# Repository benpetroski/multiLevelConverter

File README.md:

# multiLevelConverter
A Multi-Level Converter Topology

Email benjaminpetroski@gmail.com with questions.

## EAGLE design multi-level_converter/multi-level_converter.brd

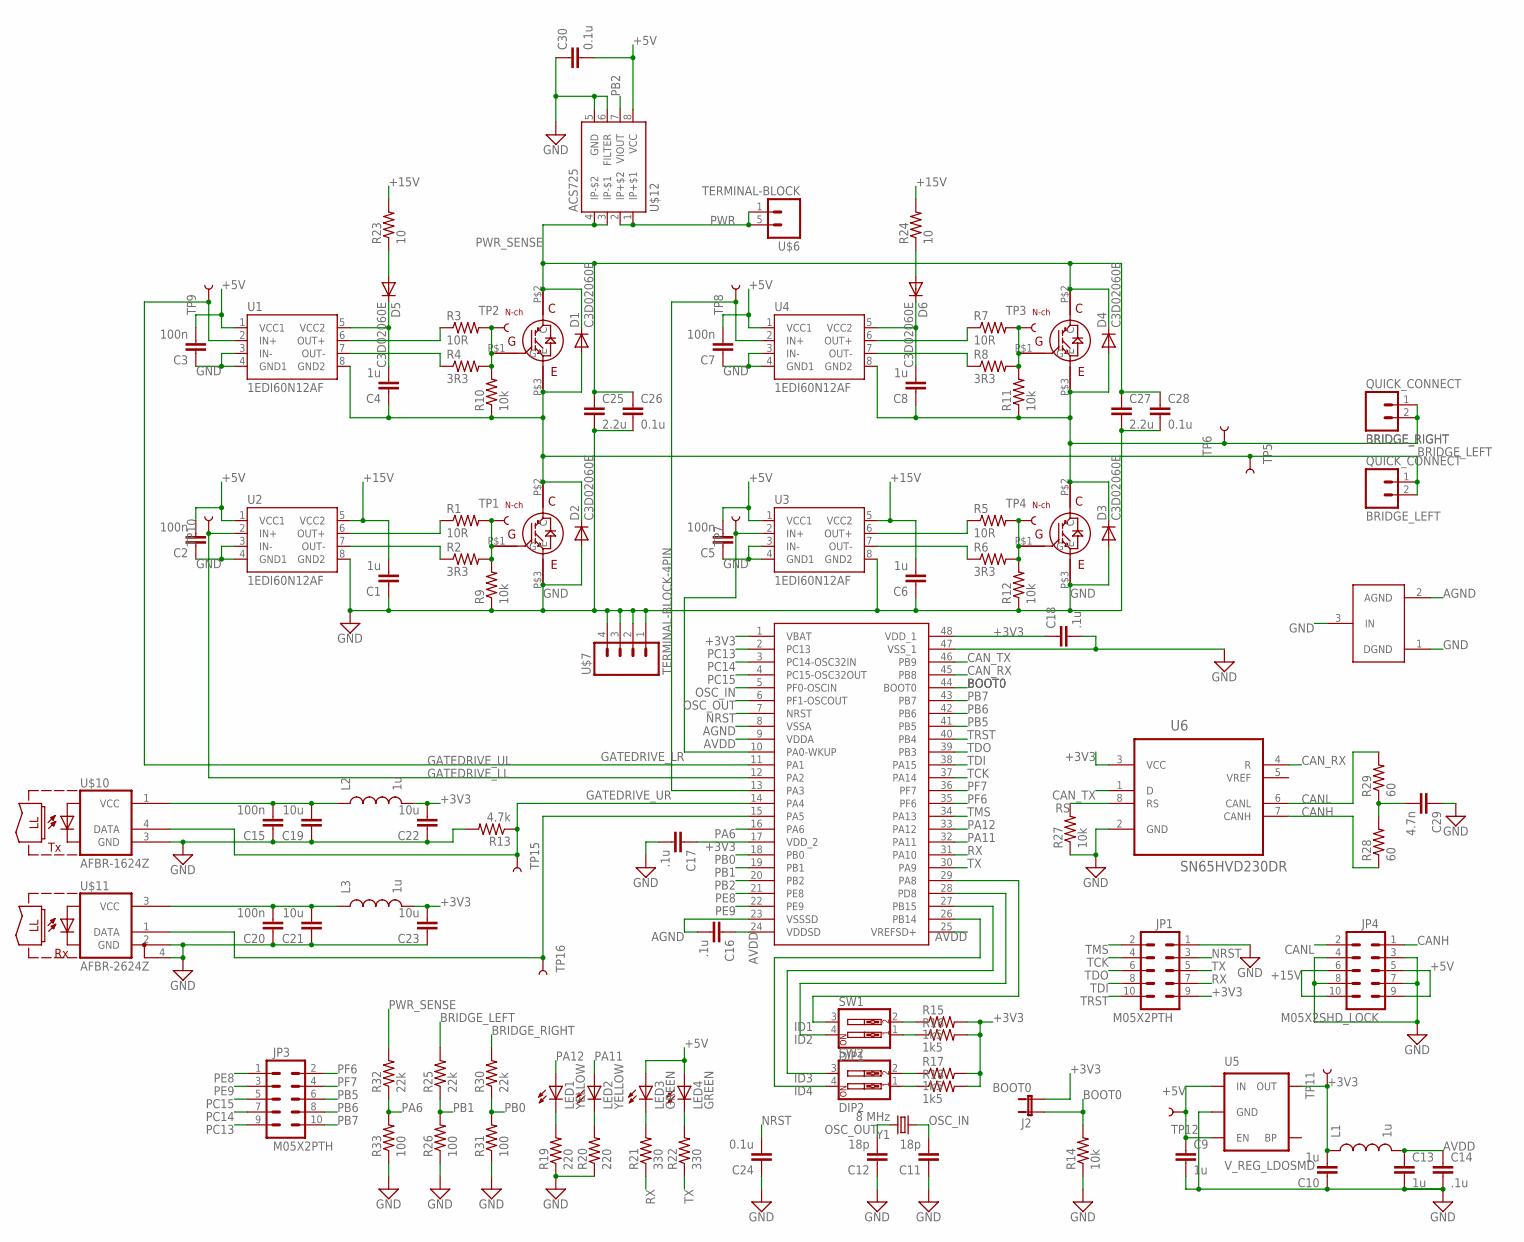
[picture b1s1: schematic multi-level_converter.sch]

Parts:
BRIDGE_LEFT: QUICK_CONNECT
BRIDGE_RIGHT: QUICK_CONNECT
C1, C4, C6, C8, C9, C10, C13: 1u; 0805
C2, C3, C5, C7, C15, C20: 100n; 0805
C11, C12: 18p; 0805
C14, C16, C17, C18: .1u; 0805
C19, C21, C22, C23: 10u; 0805
C24, C30: 0.1u; 0805
C25, C27: 2.2u; C37.5B20
C26, C28: 0.1u; C2225K
C29: 4.7n; 0805
D1, D2, D3, D4, D5, D6: C3D02060E; TO252
J1: GND_CONNECT
J2: BOOT0; 1X02
JP1, JP3: M05X2PTH; AVR_ICSP
JP4: M05X2SHD_LOCK; 2X5-SHROUDED_LOCK
L1, L2, L3: 1u; 0805
LED1, LED2: YELLOW; LED-0603
LED3, LED4: GREEN; LED-0603
R1, R3, R5, R7: 10R; 0805
R2, R4, R6, R8: 3R3; 0805
R9, R10, R11, R12, R14, R27: 10k; 0805
R13: 4.7k; 0805
R15, R16, R17, R18: 1k5; 0805
R19, R20: 220; 0805
R21, R22: 330; 0805
R23, R24: 10; 0805
R25, R30, R32: 22k; 0805
R26, R31, R33: 100; 0805
R28, R29: 60; 0805
SW1: DIP1; DIPSWITCH-02
SW2: DIP2; DIPSWITCH-02
TP1, TP2, TP3, TP4, TP5, TP6, TP7, TP8, TP9, TP10, TP11, TP12, TP15, TP16: TEST-POINT3X5; PAD.03X.05
U1, U2, U3, U4: 1EDI60N12AF; SO08
U5: V_REG_LDOSMD; SOT23-5
U6: SN65HVD230DR; SOIC127P600X175-8N
U$1, U$2, U$3, U$4: TO-247B; TO-247-FLAT
U$5: STM32F373CCT6; LQFP48
U$6: TERMINAL-BLOCK; 10MM_2PIN_CONNECTOR
U$7: TERMINAL-BLOCK-4PIN; 10MM_4PIN_CONNECTOR
U$10: AFBR-1624Z; HFBR-15X3
U$11: AFBR-2624Z; HFBR-15X3
U$12: ACS725; SO08
Y1: 8 MHz; HC49UP

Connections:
+3V3: C10.2, C17.1, C18.1, C22.2, C23.2, J2.2, JP1.9, L1.1, L2.2, L3.2, R15.2, R16.2, R17.2, R18.2, TP11.P$1, U5.VS (OUT), U6.3 (VCC), U$5.1 (VBAT), U$5.17 (VDD_2), U$5.48 (VDD_1)
+5V: C2.2, C3.2, C5.2, C7.2, C9.1, C30.2, JP4.5, JP4.9, LED3.A, LED4.A, TP12.P$1, U1.1 (VCC1), U2.1 (VCC1), U3.1 (VCC1), U4.1 (VCC1), U5.CS (IN), U5.GATE (EN), U$12.8 (VCC)
+15V: C1.2, C6.2, JP4.6, JP4.10, R23.2, R24.2, U2.5 (VCC2), U3.5 (VCC2)
AGND: C16.2, J1.2 (AGND), U$5.8 (VSSA), U$5.23 (VSSSD)
AVDD: C13.1, C14.1, C16.1, L1.2, U$5.9 (VDDA), U$5.24 (VDDSD), U$5.25 (VREFSD+)
BOOT0: J2.1, R14.2, U$5.44 (BOOT0)
BRIDGE_LEFT: BRIDGE_LEFT.1, BRIDGE_LEFT.2, C4.1, D1.2 (A), D2.1 (C), D2.3 (C), R10.1, R25.2, TP5.P$1, U1.8 (GND2), U$1.P$3 (E), U$3.P$2 (C)
BRIDGE_RIGHT: BRIDGE_RIGHT.1, BRIDGE_RIGHT.2, C8.1, D3.1 (C), D3.3 (C), D4.2 (A), R11.1, R30.2, TP6.P$1, U4.8 (GND2), U$2.P$2 (C), U$4.P$3 (E)
CANH: JP4.1, R28.1, U6.7 (CANH)
CANL: JP4.2, R29.2, U6.6 (CANL)
CAN_RX: U6.4 (R), U$5.45 (PB8)
CAN_TX: U6.1 (D), U$5.46 (PB9)
GATEDRIVE_LL: TP10.P$1, U2.2 (IN+), U$5.12 (PA2)
GATEDRIVE_LR: TP7.P$1, U3.2 (IN+), U$5.10 (PA0-WKUP)
GATEDRIVE_UL: TP9.P$1, U1.2 (IN+), U$5.11 (PA1)
GATEDRIVE_UR: TP8.P$1, U4.2 (IN+), U$5.13 (PA3)
GND: C1.1, C2.1, C3.1, C5.1, C6.1, C7.1, C9.2, C10.1, C11.1, C12.1, C13.2, C14.2, C15.1, C17.2, C18.2, C19.1, C20.1, C21.1, C22.1, C23.1, C24.1, C25.2, C26.2, C27.2, C28.2, C29.1, C30.1, D2.2 (A), D3.2 (A), J1.1 (DGND), J1.3 (IN), JP1.1, JP4.3, JP4.4, JP4.7, JP4.8, R9.1, R12.1, R13.2, R14.1, R19.1, R20.1, R26.1, R27.1, R31.1, R33.1, U1.3 (IN-), U1.4 (GND1), U2.3 (IN-), U2.4 (GND1), U2.8 (GND2), U3.3 (IN-), U3.4 (GND1), U3.8 (GND2), U4.3 (IN-), U4.4 (GND1), U5.N/C (GND), U6.2 (GND), U$2.P$3 (E), U$3.P$3 (E), U$5.47 (VSS_1), U$7.1, U$7.2, U$7.3, U$7.4, U$10.3 (GND), U$11.2 (GND), U$11.4 (GND1), U$12.5 (GND), U$12.6 (FILTER)
G_LL: R1.2, R2.2, R9.2, TP1.P$1, U$3.P$1 (G)
G_LR: R5.2, R6.2, R12.2, TP4.P$1, U$2.P$1 (G)
G_UL: R3.2, R4.2, R10.2, TP2.P$1, U$1.P$1 (G)
G_UR: R7.2, R8.2, R11.2, TP3.P$1, U$4.P$1 (G)
ID1: SW1.3, U$5.29 (PA8)
ID2: SW1.4, U$5.28 (PD8)
ID3: SW2.3, U$5.27 (PB15)
ID4: SW2.4, U$5.26 (PB14)
unnamed: C8.2, D6.1 (C), D6.3 (C), U4.5 (VCC2)
unnamed: R1.1, U2.6 (OUT+)
unnamed: R2.1, U2.7 (OUT-)
unnamed: R3.1, U1.6 (OUT+)
unnamed: R4.1, U1.7 (OUT-)
unnamed: R5.1, U3.6 (OUT+)
unnamed: R6.1, U3.7 (OUT-)
unnamed: R7.1, U4.6 (OUT+)
unnamed: R8.1, U4.7 (OUT-)
unnamed: LED3.C, R21.2
unnamed: LED4.C, R22.2
unnamed: R15.1, SW1.2
unnamed: R16.1, SW1.1
unnamed: R17.1, SW2.2
unnamed: R18.1, SW2.1
unnamed: C15.2, C19.2, L2.1, U$10.1 (VCC)
unnamed: C20.2, C21.2, L3.1, U$11.3 (VCC)
unnamed: R13.1, TP15.P$1, U$5.14 (PA4), U$10.4 (DATA)
unnamed: TP16.P$1, U$5.15 (PA5), U$11.1 (DATA)
unnamed: LED1.C, R19.2
unnamed: LED2.C, R20.2
unnamed: D5.2 (A), R23.1
unnamed: C4.2, D5.1 (C), D5.3 (C), U1.5 (VCC2)
unnamed: D6.2 (A), R24.1
unnamed: C29.2, R28.2, R29.1
NRST: C24.2, JP1.3, U$5.7 (NRST)
OSC_IN: C11.2, U$5.5 (PF0-OSCIN), Y1.1
OSC_OUT: C12.2, U$5.6 (PF1-OSCOUT), Y1.2
PA6: R32.1, R33.2, U$5.16 (PA6)
PA11: LED2.A, U$5.32 (PA11)
PA12: LED1.A, U$5.33 (PA12)
PB0: R30.1, R31.2, U$5.18 (PB0)
PB1: R25.1, R26.2, U$5.19 (PB1)
PB2: U$5.20 (PB2), U$12.7 (VIOUT)
PB5: JP3.6, U$5.41 (PB5)
PB6: JP3.8, U$5.42 (PB6)
PB7: JP3.10, U$5.43 (PB7)
PC13: JP3.9, U$5.2 (PC13)
PC14: JP3.7, U$5.3 (PC14-OSC32IN)
PC15: JP3.5, U$5.4 (PC15-OSC32OUT)
PE8: JP3.1, U$5.21 (PE8)
PE9: JP3.3, U$5.22 (PE9)
PF6: JP3.2, U$5.35 (PF6)
PF7: JP3.4, U$5.36 (PF7)
PWR: U$6.1, U$6.5 (2), U$12.1 (IP+$1), U$12.2 (IP+$2)
PWR_SENSE: C25.1, C26.1, C27.1, C28.1, D1.1 (C), D1.3 (C), D4.1 (C), D4.3 (C), R32.2, U$1.P$2 (C), U$4.P$2 (C), U$12.3 (IP-$1), U$12.4 (IP-$2)
RS: R27.2, U6.8 (RS)
RX: JP1.7, R21.1, U$5.31 (PA10)
TCK: JP1.4, U$5.37 (PA14)
TDI: JP1.8, U$5.38 (PA15)
TDO: JP1.6, U$5.39 (PB3)
TMS: JP1.2, U$5.34 (PA13)
TRST: JP1.10, U$5.40 (PB4)
TX: JP1.5, R22.1, U$5.30 (PA9)

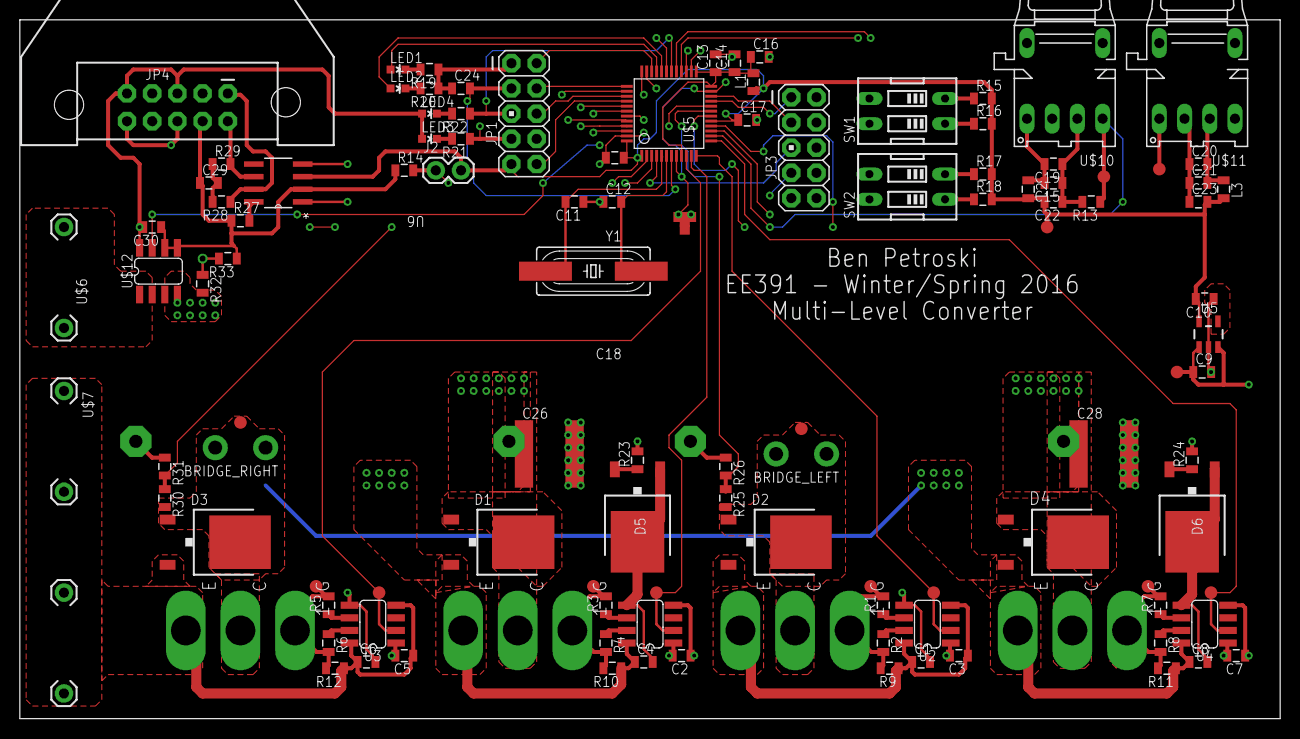
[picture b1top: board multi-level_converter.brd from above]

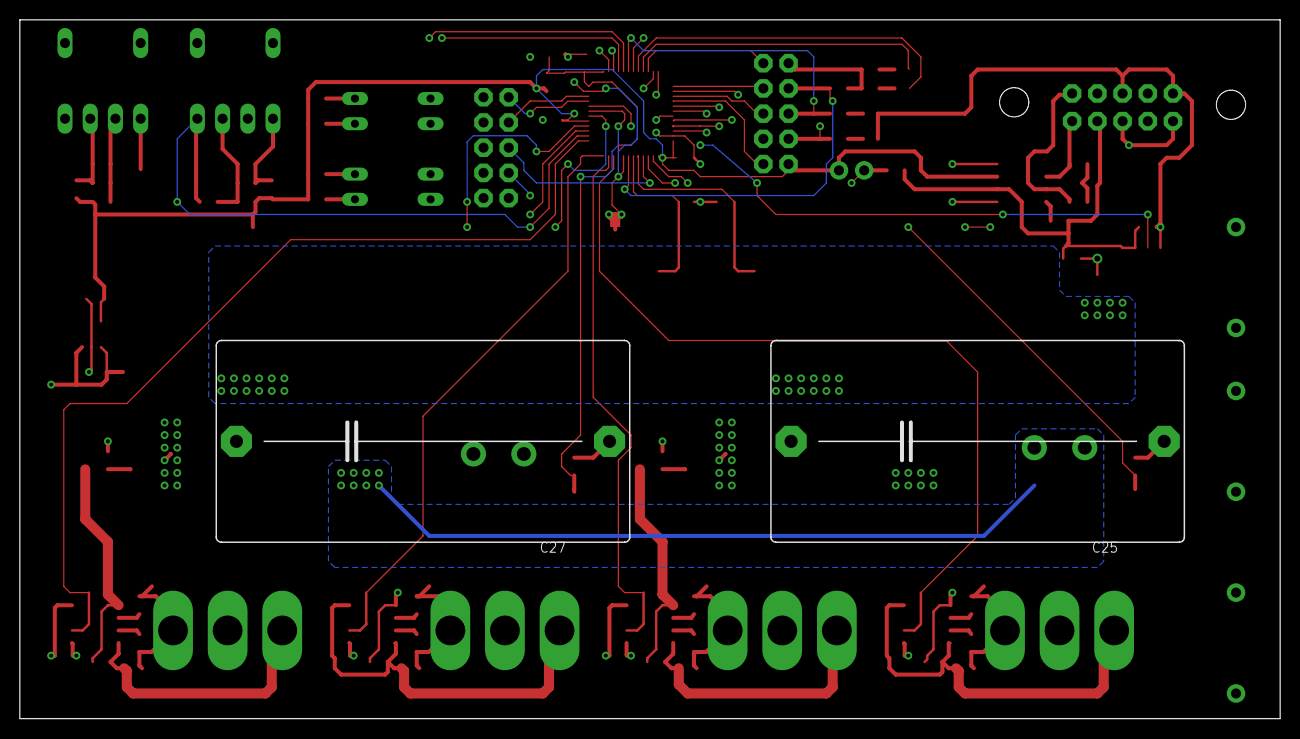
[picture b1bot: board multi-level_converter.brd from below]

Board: 4 copper layers, 127.0 x 70.4 mm, 116 parts (2 on the bottom side), 79 nets.

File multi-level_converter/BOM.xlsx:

| Part | Value | Device | Package | Description
 | BRIDGE_LEFT | QUICK_CONNECT | QUICK_CONNECT | QUICK_CONNECT
 | BRIDGE_RIGHT | QUICK_CONNECT | QUICK_CONNECT | QUICK_CONNECT
 | C1 | 1u | CAP0805 | 805 | Capacitor
 | C2 | 100n | CAP0805 | 805 | Capacitor
 | C3 | 100n | CAP0805 | 805 | Capacitor
 | C4 | 1u | CAP0805 | 805 | Capacitor
 | C5 | 100n | CAP0805 | 805 | Capacitor
 | C6 | 1u | CAP0805 | 805 | Capacitor
 | C7 | 100n | CAP0805 | 805 | Capacitor
 | C8 | 1u | CAP0805 | 805 | Capacitor
 | C9 | 1u | CAP0805 | 805 | Capacitor
 | C10 | 1u | CAP0805 | 805 | Capacitor
 | C11 | 18p | CAP0805 | 805 | Capacitor
 | C12 | 18p | CAP0805 | 805 | Capacitor
 | C13 | 1u | CAP0805 | 805 | Capacitor
 | C14 | .1u | CAP0805 | 805 | Capacitor
 | C15 | 100n | CAP0805 | 805 | Capacitor
 | C16 | .1u | CAP0805 | 805 | Capacitor
 | C17 | .1u | CAP0805 | 805 | Capacitor
 | C18 | .1u | CAP0805 | 805 | Capacitor
 | C19 | 10u | CAP0805 | 805 | Capacitor
 | C20 | 100n | CAP0805 | 805 | Capacitor
 | C21 | 10u | CAP0805 | 805 | Capacitor
 | C22 | 10u | CAP0805 | 805 | Capacitor
 | C23 | 10u | CAP0805 | 805 | Capacitor
 | C24 | 0.1u | CAP0805 | 805 | Capacitor
 | C25 | 2.2u | C37/20 | C37.5B20 | CAPACITOR
 | C26 | 0.1u | C-EUC2225K | C2225K | CAPACITOR, European symbol
 | C27 | 2.2u | C37/20 | C37.5B20 | CAPACITOR
 | C28 | 0.1u | C-EUC2225K | C2225K | CAPACITOR, European symbol
 | C29 | 4.7n | CAP0805 | 805 | Capacitor
 | C30 | 0.1u | CAP0805 | 805 | Capacitor
 | D1 | C3D02060E | C3D02060E | TO252
 | D2 | C3D02060E | C3D02060E | TO252
 | D3 | C3D02060E | C3D02060E | TO252
 | D4 | C3D02060E | C3D02060E | TO252
 | D5 | C3D02060E | C3D02060E | TO252
 | D6 | C3D02060E | C3D02060E | TO252
 | J1 | GND_CONNECT | GND_CONNECT | GND_CONNECT
 | J2 | BOOT0 | JUMPER-2PTH | 1X02 | Jumper
 | JP1 | M05X2PTH | M05X2PTH | AVR_ICSP | Header 5x2
 | JP3 | M05X2PTH | M05X2PTH | AVR_ICSP | Header 5x2
 | JP4 | M05X2SHD_LOCK | M05X2SHD_LOCK | 2X5-SHROUDED_LOCK | Header 5x2
 | L1 | 1u | INDUCTOR0805 | 805 | Inductors
 | L2 | 1u | INDUCTOR0805 | 805 | Inductors
 | L3 | 1u | INDUCTOR0805 | 805 | Inductors
 | LED1 | YELLOW | LED0603 | LED-0603 | LEDs
 | LED2 | YELLOW | LED0603 | LED-0603 | LEDs
 | LED3 | GREEN | LED0603 | LED-0603 | LEDs
 | LED4 | GREEN | LED0603 | LED-0603 | LEDs
 | R1 | 10R | RESISTOR0805-RES | 805 | Resistor
 | R2 | 3R3 | RESISTOR0805-RES | 805 | Resistor
 | R3 | 10R | RESISTOR0805-RES | 805 | Resistor
 | R4 | 3R3 | RESISTOR0805-RES | 805 | Resistor
 | R5 | 10R | RESISTOR0805-RES | 805 | Resistor
 | R6 | 3R3 | RESISTOR0805-RES | 805 | Resistor
 | R7 | 10R | RESISTOR0805-RES | 805 | Resistor
 | R8 | 3R3 | RESISTOR0805-RES | 805 | Resistor
 | R9 | 10k | RESISTOR0805-RES | 805 | Resistor
 | R10 | 10k | RESISTOR0805-RES | 805 | Resistor
 | R11 | 10k | RESISTOR0805-RES | 805 | Resistor
 | R12 | 10k | RESISTOR0805-RES | 805 | Resistor
 | R13 | 4.7k | RESISTOR0805-RES | 805 | Resistor
 | R14 | 10k | RESISTOR0805-RES | 805 | Resistor
 | R15 | 1k5 | RESISTOR0805-RES | 805 | Resistor
 | R16 | 1k5 | RESISTOR0805-RES | 805 | Resistor
 | R17 | 1k5 | RESISTOR0805-RES | 805 | Resistor
 | R18 | 1k5 | RESISTOR0805-RES | 805 | Resistor
 | R19 | 220 | RESISTOR0805-RES | 805 | Resistor
 | R20 | 220 | RESISTOR0805-RES | 805 | Resistor
 | R21 | 330 | RESISTOR0805-RES | 805 | Resistor
 | R22 | 330 | RESISTOR0805-RES | 805 | Resistor
 | R23 | 10 | RESISTOR0805-RES | 805 | Resistor
 | R24 | 10 | RESISTOR0805-RES | 805 | Resistor
 | R25 | 22k | RESISTOR0805-RES | 805 | Resistor
 | R26 | 100 | RESISTOR0805-RES | 805 | Resistor
 | R27 | 10k | RESISTOR0805-RES | 805 | Resistor
 | R28 | 60 | RESISTOR0805-RES | 805 | Resistor
 | R29 | 60 | RESISTOR0805-RES | 805 | Resistor
 | R30 | 22k | RESISTOR0805-RES | 805 | Resistor
 | R31 | 100 | RESISTOR0805-RES | 805 | Resistor
 | R32 | 22k | RESISTOR0805-RES | 805 | Resistor
 | R33 | 100 | RESISTOR0805-RES | 805 | Resistor
 | SW1 | DIP1 | SW_DIP-2 | DIPSWITCH-02 | DIP SWITCH
 | SW2 | DIP2 | SW_DIP-2 | DIPSWITCH-02 | DIP SWITCH
 | TP1 | TEST-POINT3X5 | TEST-POINT3X5 | PAD.03X.05
 | TP2 | TEST-POINT3X5 | TEST-POINT3X5 | PAD.03X.05
 | TP3 | TEST-POINT3X5 | TEST-POINT3X5 | PAD.03X.05
 | TP4 | TEST-POINT3X5 | TEST-POINT3X5 | PAD.03X.05
 | TP5 | TEST-POINT3X5 | TEST-POINT3X5 | PAD.03X.05
 | TP6 | TEST-POINT3X5 | TEST-POINT3X5 | PAD.03X.05
 | TP7 | TEST-POINT3X5 | TEST-POINT3X5 | PAD.03X.05
 | TP8 | TEST-POINT3X5 | TEST-POINT3X5 | PAD.03X.05
 | TP9 | TEST-POINT3X5 | TEST-POINT3X5 | PAD.03X.05
 | TP10 | TEST-POINT3X5 | TEST-POINT3X5 | PAD.03X.05
 | TP11 | TEST-POINT3X5 | TEST-POINT3X5 | PAD.03X.05
 | TP12 | TEST-POINT3X5 | TEST-POINT3X5 | PAD.03X.05
 | TP15 | TEST-POINT3X5 | TEST-POINT3X5 | PAD.03X.05
 | TP16 | TEST-POINT3X5 | TEST-POINT3X5 | PAD.03X.05
 | U$1 | TO-247B | TO-247B | TO-247-FLAT
 | U$2 | TO-247B | TO-247B | TO-247-FLAT
 | U$3 | TO-247B | TO-247B | TO-247-FLAT
 | U$4 | TO-247B | TO-247B | TO-247-FLAT
 | U$5 | STM32F373CCT6 | STM32F373CCT6 | LQFP48
 | U$6 | TERMINAL-BLOCK | TERMINAL-BLOCK | 10MM_2PIN_CONNECTOR
 | U$7 | TERMINAL-BLOCK-4PIN | TERMINAL-BLOCK-4PIN | 10MM_4PIN_CONNECTOR
 | U$10 | AFBR-1624Z | AFBR-1624Z | HFBR-15X3
 | U$11 | AFBR-2624Z | AFBR-2624Z | HFBR-15X3
 | U$12 | ACS725 | ACS725 | SO08
 | U1 | 1EDI60N12AF | 1EDI60N12AF | SO08
 | U2 | 1EDI60N12AF | 1EDI60N12AF | SO08
 | U3 | 1EDI60N12AF | 1EDI60N12AF | SO08
 | U4 | 1EDI60N12AF | 1EDI60N12AF | SO08
 | U5 | V_REG_LDOSMD | V_REG_LDOSMD | SOT23-5 | Voltage Regulator LDO
 | U6 | SN65HVD230DR | SN65HVD230DR | SOIC127P600X175-8N | 3.3-V CAN TRANSCEIVERS
 | Y1 | 8 MHz | CRYSTALSMD | HC49UP | Crystals

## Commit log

2016-06-10 adding code and eagle files
